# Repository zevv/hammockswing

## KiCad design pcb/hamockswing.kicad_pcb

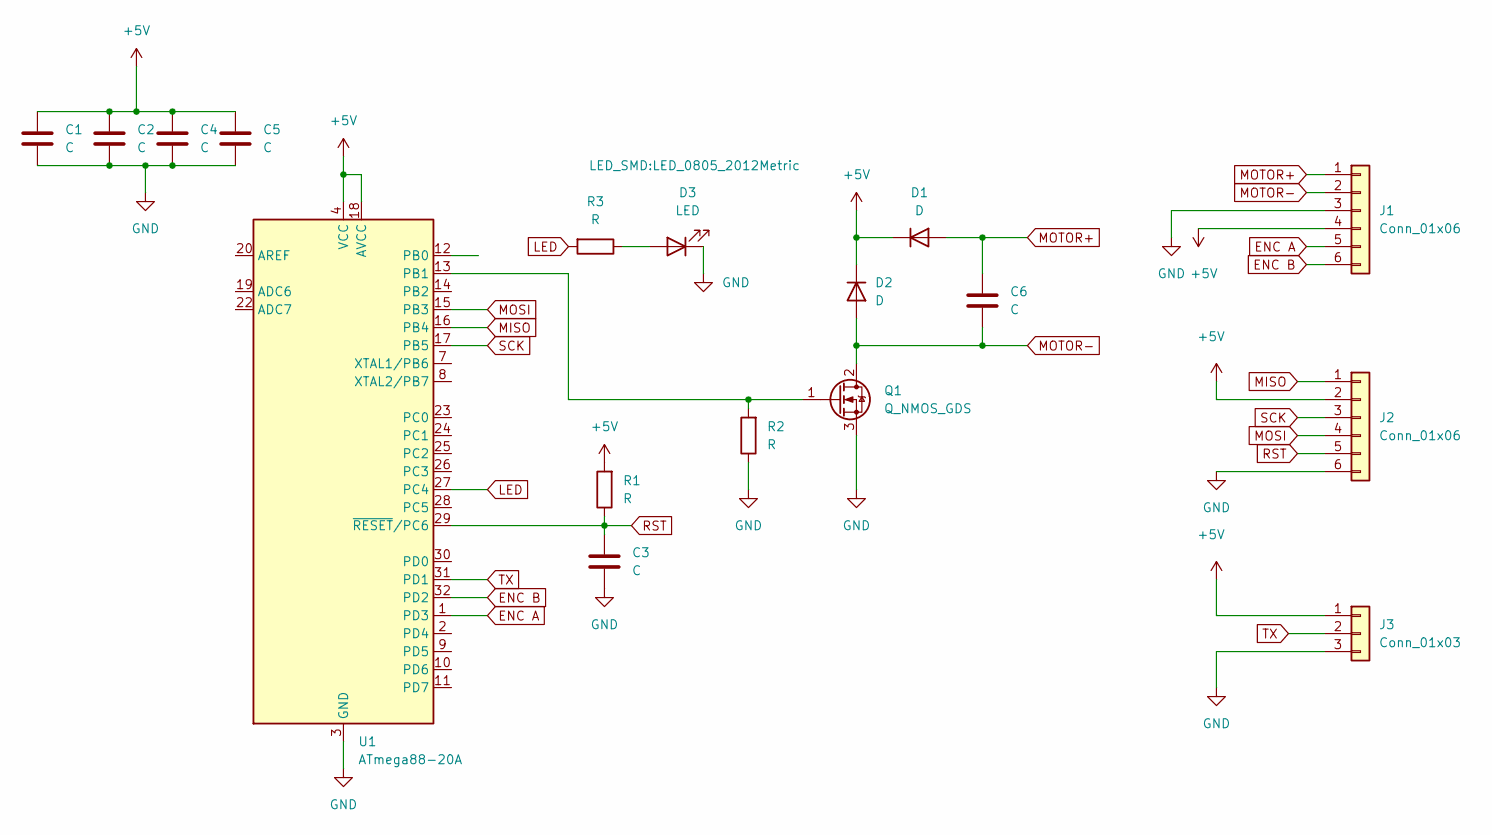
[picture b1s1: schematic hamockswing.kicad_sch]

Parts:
C1, C2, C3, C6: C; C_0603_1608Metric
C4, C5: C; C_0805_2012Metric
D1, D2: D; D_SOD-123F
D3: LED; LED_0805_2012Metric
J1: Conn_01x06; PinHeader_1x06_P2.54mm_Horizontal
J2: Conn_01x06; PinHeader_2x03_P2.54mm_Vertical
J3: Conn_01x03; PinHeader_1x03_P2.54mm_Horizontal
Q1: Q_NMOS_GDS; SOT-223
R1, R2, R3: R; R_0603_1608Metric
U1: ATmega88-20A; TQFP-32_7x7mm_P0.8mm

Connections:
+5V: C1.2, C2.2, C4.2, C5.2, D1.1 (K), D2.1 (K), J1.4, J2.2, J3.1, R1.2, U1.4 (VCC), U1.6 (VCC), U1.18 (AVCC)
ENC A: J1.5, U1.1 (PD3)
ENC B: J1.6, U1.32 (PD2)
GND: C1.1, C2.1, C3.1, C4.1, C5.1, D3.1 (K), J1.3, J2.6, J3.3, Q1.3 (S), R2.1, U1.3 (GND), U1.5 (GND), U1.21 (GND)
LED: R3.2, U1.27 (PC4)
MISO: J2.1, U1.16 (PB4)
MOSI: J2.4, U1.15 (PB3)
MOTOR+: C6.2, D1.2 (A), J1.1
MOTOR-: C6.1, D2.2 (A), J1.2, Q1.2 (D)
unnamed: D3.2 (A), R3.1
unnamed: Q1.1 (G), R2.2, U1.13 (PB1)
RST: C3.2, J2.5, R1.1, U1.29 (~RESET/PC6)
SCK: J2.3, U1.17 (PB5)
TX: J3.2, U1.31 (PD1)

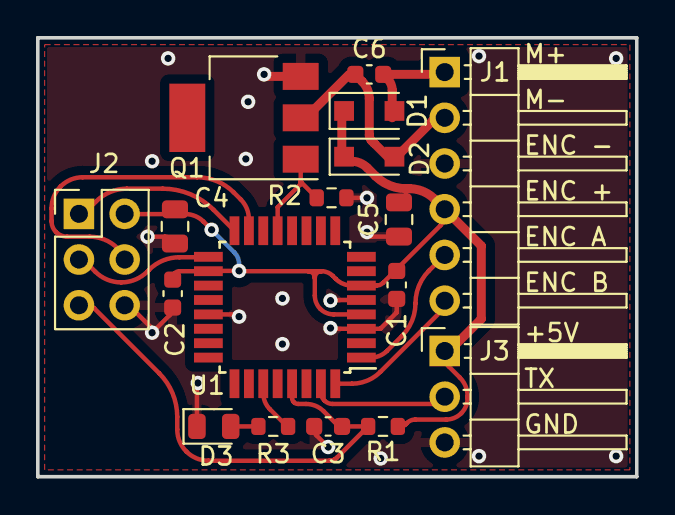
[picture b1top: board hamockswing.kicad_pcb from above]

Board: 2 copper layers, 33.3 x 24.4 mm, 17 parts (0 on the bottom side), 14 nets.

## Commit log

2022-07-05 checkin
2022-07-05 stuff
2022-07-05 Edges
2022-07-05 encoder
2022-07-05 gitignore
2022-07-05 pdf:
2022-07-08 swing
2022-07-09 better
2022-07-10 bootloader
2022-07-10 moved src
2022-07-10 Schem1
2022-07-12 kind of works, pcb as delivered to eurocircuits
2022-07-12 jerk opt
2022-07-12 Flop
2022-07-13 Added blend
2022-07-22 perfect
2022-07-22 State machine
2022-07-22 fixnshit
2022-07-22 betterder
2022-07-23 power set
2022-07-23 hieght pid
